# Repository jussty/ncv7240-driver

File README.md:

# NCV7240 x4 — ESP32 + USB-C PD EPR (24 V) Driver Board

A KiCad 8 project for a compact controller board that:

- Negotiates **24 V** from a USB-C **PD 3.1 EPR** source via the **AP33772S** sink controller.
- Hosts an **ESP32-S3** MCU for Wi-Fi/BT control, configuration and host comms.
- Drives **32 low-side switched outputs** at 24 V using **4 × NCV7240** octal low-side drivers (SPI-controlled).

> Status: skeleton — project files, design rules, net classes and BOM are in place. The schematic (`ncv7240-driver.kicad_sch`) and PCB (`ncv7240-driver.kicad_pcb`) are intentionally empty placeholders ready to be populated in KiCad 8.

---

## 1. System architecture

```
       USB-C (PD 3.1 EPR, up to 28 V / 5 A)
           │
           ▼
   ┌────────────────┐   I²C   ┌──────────────────────┐
   │   AP33772S     │◀───────▶│   ESP32-S3-WROOM-1   │
   │  PD EPR sink   │  (CFG)  │  (Wi-Fi / BT / USB)  │
   └──────┬─────────┘         └───────┬──────────────┘
          │ VBUS_OUT = 24 V           │ SPI (CS x4, SCK, MOSI, MISO)
          │                           │ + RSTB, /FSO IRQ
          ▼                           ▼
   ┌──────────────┐   ┌──────────────┐   ┌──────────────┐   ┌──────────────┐
   │  NCV7240 #1  │   │  NCV7240 #2  │   │  NCV7240 #3  │   │  NCV7240 #4  │
   │ 8 ch low-side│   │ 8 ch low-side│   │ 8 ch low-side│   │ 8 ch low-side│
   └──────┬───────┘   └──────┬───────┘   └──────┬───────┘   └──────┬───────┘
          ▼                  ▼                  ▼                  ▼
       OUT1..8            OUT9..16          OUT17..24          OUT25..32
       (loads sink to GND; common rail = 24 V)
```

- The AP33772S handles all CC negotiation/PPS/EPR; the ESP32 just configures the
  request profile over I²C and reads VBUS / status telemetry.
- The 4 NCV7240s share SCK/MOSI/MISO/RSTB/SI on a single SPI bus; each has its
  own **/CSB** from the ESP32. Output enable is per-channel via SPI control word.

## 2. Bill of materials (core)

| Ref       | Part                          | Pkg          | Notes                                    |
|-----------|-------------------------------|--------------|------------------------------------------|
| U1        | AP33772S                      | QFN-24       | USB-C PD 3.1 EPR sink controller         |
| U2        | ESP32-S3-WROOM-1-N8R8         | SMD module   | 8 MB flash, 8 MB PSRAM                   |
| U3..U6    | NCV7240ADQR2G                 | SSOP-24      | Octal low-side driver, SPI               |
| J1        | USB-C receptacle (EPR rated)  | TID/16-pin   | 5 A continuous, EPR cable required >3 A  |
| D1        | TVS for VBUS (e.g. SMBJ33A)   | SMB          | 33 V standoff                            |
| L1        | 10 µH @ 3 A ferrite/inductor  | 1210         | VBUS LC filter (optional)                |
| C_BULK    | 100 µF / 50 V × 2             | electrolytic | VBUS bulk on 24 V rail                   |
| FB1..FB4  | Ferrite bead, 600 Ω @ 100 MHz | 0603         | Per-NCV7240 V_PWR decoupling             |
| U7        | LDO/buck 24 V → 3.3 V (e.g. MP2451 or TPS62932) | SOT-23-6 | ≥500 mA for ESP32 peaks    |
| U8        | (optional) 3.3 V LDO          | SOT-23-5     | Clean rail for analog if needed          |
| Q_GATE    | P-MOSFET (e.g. DMP3098L)      | SOT-23       | Reverse-polarity / VBUS gate (optional)  |
| R_CS      | 1 % shunts                    | 0805         | If per-bank current sensing is desired   |

Plus per-channel flyback diodes/TVS if driving inductive loads (the NCV7240
has internal active clamp, but external TVS to 24 V rail is recommended for
solenoids/relays).

## 3. Net classes / design rules

Defined in `ncv7240-driver.kicad_pro`:

| Net class    | Track | Clearance | Vias        | Used for                              |
|--------------|-------|-----------|-------------|---------------------------------------|
| Default      | 0.25  | 0.20      | 0.6 / 0.3   | logic, SPI, I²C                       |
| Power_24V    | 0.80  | 0.40      | 0.9 / 0.4   | VBUS, 24 V plane feeds, OUTx pours    |
| USB_PD       | 0.40  | 0.25      | 0.7 / 0.3   | CC1/CC2, VBUS sense, D+/D- (90 Ω diff)|

## 4. Pin assignment (ESP32-S3 → NCVs / AP33772S)

| ESP32 pin | Net           | Goes to                                  |
|-----------|---------------|------------------------------------------|
| GPIO10    | SPI_CS1       | NCV7240 #1 /CSB                          |
| GPIO11    | SPI_CS2       | NCV7240 #2 /CSB                          |
| GPIO12    | SPI_CS3       | NCV7240 #3 /CSB                          |
| GPIO13    | SPI_CS4       | NCV7240 #4 /CSB                          |
| GPIO14    | SPI_SCK       | all NCV7240 SCLK                         |
| GPIO15    | SPI_MOSI      | all NCV7240 SI                           |
| GPIO16    | SPI_MISO      | all NCV7240 SO (open-drain, ext. pull-up)|
| GPIO17    | NCV_RSTB      | all NCV7240 /RSTB (active low, pull-up)  |
| GPIO18    | NCV_FSO       | all NCV7240 /FSO fault flag (IRQ)        |
| GPIO8     | I2C_SDA       | AP33772S SDA (+ 4.7 kΩ pull-up to 3V3)   |
| GPIO9     | I2C_SCL       | AP33772S SCL (+ 4.7 kΩ pull-up to 3V3)   |
| GPIO4     | PD_INT        | AP33772S /INT                            |
| EN        | reset btn     | per ESP32 standard wiring                |
| GPIO0     | boot btn      | per ESP32 standard wiring                |

> Avoid the strapping pins (GPIO0/3/45/46) and USB pins (19/20) for the
> dedicated nets above — already accounted for.

## 5. NCV7240 wiring notes

- Tie all `V_PWR` pins to the 24 V rail through individual ferrite beads
  + 100 nF + 10 µF local decoupling per IC.
- All `GND` pins tied to the solid 24 V-return ground pour.
- `SO` is open-drain; place one 10 kΩ pull-up to 3V3 on the shared MISO net.
- `/RSTB` shared and pulled up to 3V3 (10 kΩ); ESP32 drives low to reset all.
- `/FSO` shared open-drain fault flag → ESP32 IRQ, pulled up to 3V3.
- Daisy-chained SPI is **not** used here (independent /CSB per device is
  simpler and lets the ESP32 talk to any device individually at full clock).
- Each OUTx pad gets a generous copper pour and a screw terminal or 2.54 mm
  header per channel. For inductive loads, place a TVS/clamp diode from OUTx
  to the 24 V rail close to the load connector.

## 6. AP33772S notes

- Connect CC1/CC2 directly to the USB-C receptacle CC pins (no Rd needed —
  the AP33772S provides the sink termination).
- VBUS sense via internal divider; place 100 µF + 10 µF + 100 nF bulk on
  VBUS_OUT after the controller's NMOS pass switch.
- Pull `VPP` / `VDD` decoupling per datasheet (1 µF on VDD, 100 nF on VPP).
- The MCU configures the requested PDO (request 24 V/3 A EPR profile) via I²C
  at boot. Until configured the AP33772S falls back to its NVM defaults — flash
  the NVM with the desired default PDO request before deployment if you want
  the rail to come up without the ESP32.
- Add a SMBJ33A TVS across VBUS_OUT to GND.

## 7. Layout guidance

- 4-layer stack recommended: **Signal / GND / 24 V / Signal**.
- Keep the 24 V rail as a continuous pour on an inner layer; stitch with vias
  near each NCV7240 V_PWR pin.
- USB-C D+/D- routed as a 90 Ω differential pair, length-matched, away from
  the switching loads. (For PD-only operation D± are unused but route them
  anyway so the port can carry USB 2.0 data if desired.)
- Place the AP33772S close to the USB-C connector; keep the VBUS path short
  and wide (≥ 60 mil for 5 A).
- ESP32 antenna keep-out: leave ≥ 15 mm clearance and no copper under the
  antenna section of the module.
- Per-channel output traces: 0.8 mm minimum for 0.5 A loads, scale up for
  more. Add 2× thermal-relief pads at each NCV7240 exposed pad.

## 8. Loads — Bürkert Type 0127 valves (inductive)

Outputs drive **Bürkert Type 0127 rocker solenoid valves** (24 V DC,
**3 W ⇒ ≈125 mA per coil**). 32 channels × 125 mA = **4 A peak** on the
24 V rail — that's why we request a 24 V / 3-5 A EPR profile from the source.

Because the loads are inductive, every output has a **B260A-13-F** Schottky
(60 V / 2 A, SMA) freewheel diode:

  **Anode → OUTx, Cathode → +24V rail.**

When the NCV7240's low-side switch opens, the coil's collapsing field
drives OUTx above +24 V; the diode forward-biases at ≈0.7 V and recirculates
the coil current back into the rail, clamping OUTx to roughly `+24V + Vf`.
This is faster and dissipates less per-event than relying on the NCV7240's
internal active clamp (≈45 V).

> Place the freewheel diodes physically close to the screw terminal pads so
> the loop area between coil, diode and ground is minimised — important for
> EMI on a board switching 32 inductive loads.

## 9. Files

```
ncv7240-driver/
├── .gitignore
├── README.md
├── fp-lib-table  /  sym-lib-table
├── ncv7240-driver.kicad_pro   # KiCad 8 project, design rules + net classes
├── ncv7240-driver.kicad_sch   # generated by tools/gen_sch.py
├── ncv7240-driver.kicad_pcb   # generated by tools/gen_pcb.py
├── datasheets/                # versioned vendor PDFs
│   ├── ncv7240.pdf            (onsemi)
│   ├── ap33772s.pdf           (Diodes Inc)
│   ├── esp32-s3-wroom-1.pdf   (Espressif)
│   ├── b260a.pdf              (Diodes Inc — flyback Schottky)
│   └── burkert-0127.pdf       (Bürkert — load)
└── tools/
    ├── gen_sch.py             # deterministic schematic generator
    └── gen_pcb.py             # deterministic PCB skeleton generator
```

Regenerate after editing the generators:

```sh
python3 tools/gen_sch.py > ncv7240-driver.kicad_sch
python3 tools/gen_pcb.py > ncv7240-driver.kicad_pcb
```

Open `ncv7240-driver.kicad_pro` in **KiCad 8.0 or newer**. In Pcbnew:

1. **Tools → Update PCB from Schematic** to import all 30+ footprints
   from the standard KiCad libraries (you'll need them installed locally —
   they ship with KiCad).
2. Components arrive at the origin; drag them into the marked floorplan
   zones (visible on `User.Comments`).
3. Route, fill the GND and +24V zones, run DRC, export Gerbers to `gerbers/`.

## 10. Board floorplan (160 × 100 mm, 4-layer)

```
+----------------------------------------------------------------------+
|              NCV7240 x4 Driver — 24V PD EPR    (silkscreen header)   |
|                                                                      |
|  +--------+ +-------------+ +-------------+ +--------+ +----------+  |
|  |USB-C PD| | Buck 24V→3V3| |             | |  4×    | |  Screw   |  |
|  |  J1 U1 | |  U7 L1 C3   | |  ESP32-S3   | | NCV    | |  termi-  |  |
|  | C1/C2  | +-------------+ |   U2        | | 7240   | |  nals    |  |
|  |  D1    |                 | C4 C5       | | U3-U6  | | J2..J5   |  |
|  |        | (44-90, 6-36)   | R1..R5      | |        | |          |  |
|  |        |                 |             | |        | |          |  |
|  |        | +-------------+ |             | +--------+ +----------+  |
|  |        | |             | |             | | Flyback diode field   |  |
|  |        | |    ESP32    | |             | | D2..D33  B260A-SMA    |  |
|  | (4-44, | |  (44-90,    | | (44-90,     | | (90-156,              |  |
|  |  6-60) | |   36-96)    | |  36-96)     | |  60-96)               |  |
|  +--------+ +-------------+ +-------------+ +--------+ +----------+  |
|                                                                      |
+----------------------------------------------------------------------+
```

4-layer stackup: **F.Cu / GND / +24V / B.Cu** (1.6 mm FR4, ENIG finish).

## 9. License

Hardware: CERN-OHL-S v2 (recommended) — adjust to your needs.

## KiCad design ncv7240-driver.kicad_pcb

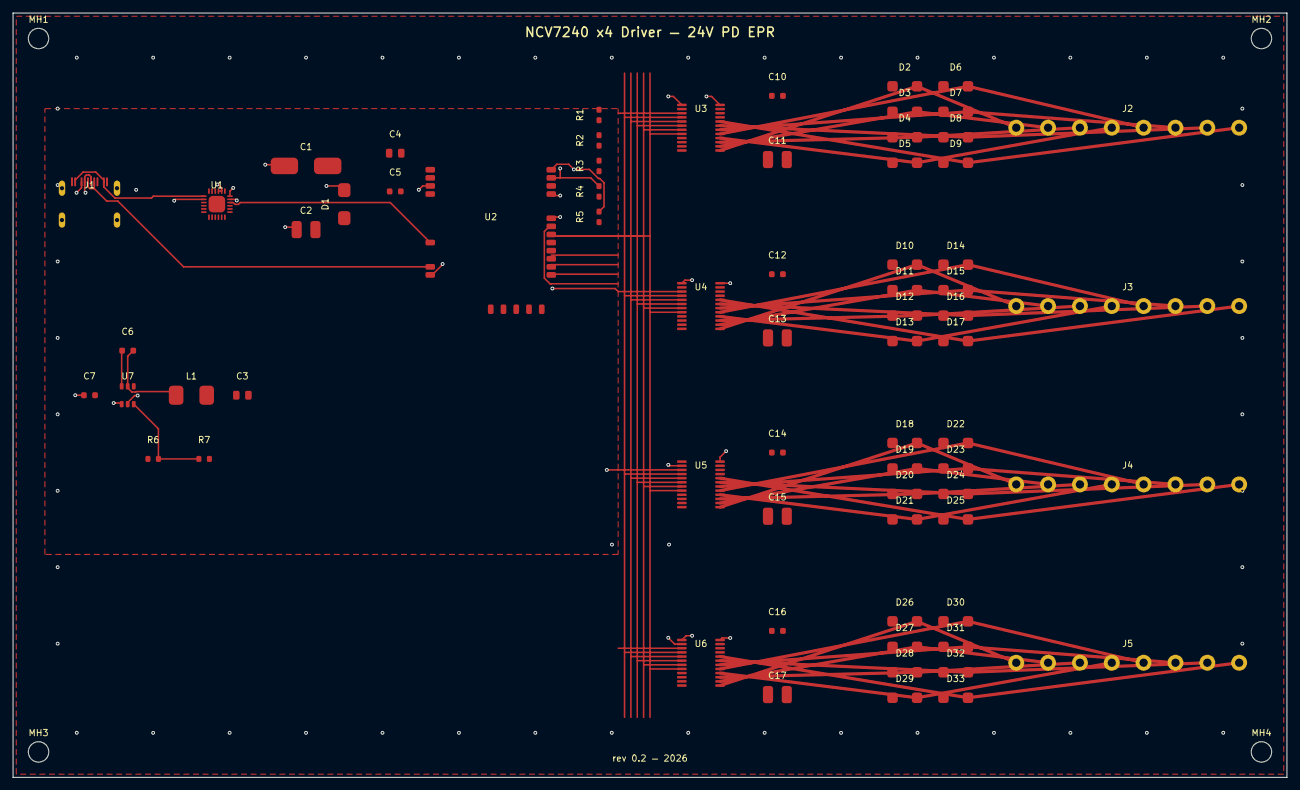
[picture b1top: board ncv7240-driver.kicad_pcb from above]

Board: 4 copper layers, 200.0 x 120.0 mm, 72 parts (0 on the bottom side), 56 nets.

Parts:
C1: 100uF/50V; CP_Elec_10x10.5
C2, C11, C13, C15, C17: 10uF/50V; C_1210_3225Metric
C3: 22uF; C_0805_2012Metric
C4: 10uF; C_0805_2012Metric
C5, C6, C7, C10, C12, C14, C16: 100nF; C_0603_1608Metric
D1: SMBJ33A; D_SMB
D2, D3, D4, D5, D6, D7, D8, D9, D10, D11, D12, D13, D14, D15, D16, D17, D18, D19, D20, D21, D22, D23, D24, D25, D26, D27, D28, D29, D30, D31, D32, D33: B260A; D_SMA
J1: USB-C; USB_C_Receptacle_HRO_TYPE-C-31-M-12
J2: OUT1-8; TerminalBlock_Phoenix_MKDS-1,5-8_1x08_P5.00mm_Horizontal
J3: OUT9-16; TerminalBlock_Phoenix_MKDS-1,5-8_1x08_P5.00mm_Horizontal
J4: OUT17-24; TerminalBlock_Phoenix_MKDS-1,5-8_1x08_P5.00mm_Horizontal
J5: OUT25-32; TerminalBlock_Phoenix_MKDS-1,5-8_1x08_P5.00mm_Horizontal
L1: 4.7uH/2A; L_Bourns-SRN6045TA
MH1, MH2, MH3, MH4: M3; MountingHole_3.2mm_M3
R1, R2, R3: 10k; R_0603_1608Metric
R4, R5: 4.7k; R_0603_1608Metric
R6: 100k; R_0603_1608Metric
R7: 20k; R_0603_1608Metric
U1: AP33772S; QFN-24-1EP_4x4mm_P0.5mm_EP2.6x2.6mm
U2: ESP32-S3-WROOM-1
U3, U4, U5, U6: NCV7240; SSOP-24_5.3x8.2mm_P0.65mm
U7: TPS62932; SOT-23-6

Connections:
+3V3: C3.1, C4.1, C5.1, L1.2, R1.1, R2.1, R3.1, R4.1, R5.1, R6.1, U1.4, U2.2, U3.2, U4.2, U5.2, U6.2
+24V: C1.1, C2.1, C7.1, C10.1, C11.1, C12.1, C13.1, C14.1, C15.1, C16.1, C17.1, D1.2, D2.1, D3.1, D4.1, D5.1, D6.1, D7.1, D8.1, D9.1, D10.1, D11.1, D12.1, D13.1, D14.1, D15.1, D16.1, D17.1, D18.1, D19.1, D20.1, D21.1, D22.1, D23.1, D24.1, D25.1, D26.1, D27.1, D28.1, D29.1, D30.1, D31.1, D32.1, D33.1, U1.20, U1.21, U3.1, U3.24, U4.1, U4.24, U5.1, U5.24, U6.1, U6.24, U7.6
BST: C6.1, U7.1
CC1: J1.4, U1.2
CC2: J1.9, U1.3
EN_3V3: U2.3, U7.5
FB: R6.2, R7.1, U7.4
GND: C1.2, C2.2, C3.2, C4.2, C5.2, C7.2, C10.2, C11.2, C12.2, C13.2, C14.2, C15.2, C16.2, C17.2, D1.1, J1.1, J1.12, J1.SH, R7.2, U1.5, U1.6, U1.7, U1.8, U1.9, U1.10, U1.11, U1.12, U1.13, U1.14, U1.15, U1.22, U1.23, U1.24, U1.25, U2.1, U2.27, U2.37, U2.38, U2.39, U2.40, U2.41, U3.9, U3.10, U3.11, U3.12, U3.21, U3.22, U3.23, U4.9, U4.10, U4.11, U4.12, U4.21, U4.22, U4.23, U5.9, U5.10, U5.11, U5.12, U5.21, U5.22, U5.23, U6.9, U6.10, U6.11, U6.12, U6.21, U6.22, U6.23, U7.3
I2C_SCL: R5.2, U1.17, U2.17
I2C_SDA: R4.2, U1.18, U2.18
NCV_FSOB: R3.2, U2.30, U3.8, U4.8, U5.8, U6.8
NCV_RSTB: R2.2, U2.29, U3.7, U4.7, U5.7, U6.7
OUT1: D2.2, J2.1, U3.13
OUT2: D3.2, J2.2, U3.14
OUT3: D4.2, J2.3, U3.15
OUT4: D5.2, J2.4, U3.16
OUT5: D6.2, J2.5, U3.17
OUT6: D7.2, J2.6, U3.18
OUT7: D8.2, J2.7, U3.19
OUT8: D9.2, J2.8, U3.20
OUT9: D10.2, J3.1, U4.13
OUT10: D11.2, J3.2, U4.14
OUT11: D12.2, J3.3, U4.15
OUT12: D13.2, J3.4, U4.16
OUT13: D14.2, J3.5, U4.17
OUT14: D15.2, J3.6, U4.18
OUT15: D16.2, J3.7, U4.19
OUT16: D17.2, J3.8, U4.20
OUT17: D18.2, J4.1, U5.13
OUT18: D19.2, J4.2, U5.14
OUT19: D20.2, J4.3, U5.15
OUT20: D21.2, J4.4, U5.16
OUT21: D22.2, J4.5, U5.17
OUT22: D23.2, J4.6, U5.18
OUT23: D24.2, J4.7, U5.19
OUT24: D25.2, J4.8, U5.20
OUT25: D26.2, J5.1, U6.13
OUT26: D27.2, J5.2, U6.14
OUT27: D28.2, J5.3, U6.15
OUT28: D29.2, J5.4, U6.16
OUT29: D30.2, J5.5, U6.17
OUT30: D31.2, J5.6, U6.18
OUT31: D32.2, J5.7, U6.19
OUT32: D33.2, J5.8, U6.20
PD_INT: U1.16, U2.10
SPI_CS1: U2.19, U3.3
SPI_CS2: U2.20, U4.3
SPI_CS3: U2.23, U5.3
SPI_CS4: U2.24, U6.3
SPI_MISO: R1.2, U2.28, U3.6, U4.6, U5.6, U6.6
SPI_MOSI: U2.26, U3.5, U4.5, U5.5, U6.5
SPI_SCK: U2.25, U3.4, U4.4, U5.4, U6.4
SW: C6.2, L1.1, U7.2
USB_D+: J1.5, J1.7, U2.14
USB_D-: J1.6, J1.8, U2.13
VBUS: J1.2, J1.11, U1.1

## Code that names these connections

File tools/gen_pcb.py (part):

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
# ---- Buck 24V → 3.3V (x=10..50, y=55..80) ----
place_sot23_6("U7", "TPS62932", 18, 60, 0, pin_nets=[
    # SOT-23-6: pin1=BST,2=SW,3=GND,4=FB,5=EN,6=VIN  (TPS62932)
    "BST","SW","GND","FB","EN_3V3","+24V"
])
place_inductor("L1", "4.7uH/2A", 28, 60, 0, "SW", "+3V3")
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    "NCV_FSOB": 100.0,
}
BUS_PIN_K = {  # pin number on NCV → k offset from top of left column
    "SPI_SCK":  3,   # pin 4
    "SPI_MOSI": 4,   # pin 5
    "SPI_MISO": 5,   # pin 6
    "NCV_RSTB": 6,   # pin 7
    "NCV_FSOB": 7,   # pin 8
}
y_top = ncv_y_centres[0] - 0.65*5.5
y_bot = ncv_y_centres[-1] + 0.65*5.5
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
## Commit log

2026-05-11 Initial KiCad project: 4x NCV7240 + ESP32-S3 + AP33772S PD EPR 24V
2026-05-11 Draw block-diagram schematic with all symbols embedded for kicanvas
    - Python generator at tools/gen_sch.py produces ncv7240-driver.kicad_sch
    - All symbol definitions embedded inline (kicanvas has no external libs)
    - Components: USB-C, AP33772S, ESP32-S3-WROOM-1, 4x NCV7240, buck reg,
    bulk/decoupling caps, TVS, pull-ups, 8-pin output screw terminals
    - Connectivity via KiCad global labels (SPI bus, I2C, power rails, OUT1..32)
    - A2 sheet, deterministic UUIDs for clean diffs
2026-05-12 Add 32 flyback diodes, real footprints, and parts datasheets
    - 32× B260A-13-F Schottky (60V / 2A SMA) freewheel diodes — one per
    output, anode→OUTx, cathode→+24V, for Bürkert Type 0127 valve coils
    (3 W @ 24 V ≈ 125 mA, inductive)
    - Footprints assigned for all parts:
    - NCV7240 SSOP-24 P0.65
    - AP33772S QFN-24 4x4 EP2.6
2026-05-12 Start PCB layout: 4-layer 160x100mm with floorplan and pours
    - tools/gen_pcb.py — deterministic PCB skeleton generator
    - 160 × 100 mm rectangular board outline on Edge.Cuts
    - 4-layer stackup: F.Cu / GND (In1) / +24V (In2) / B.Cu, 1.6 mm FR4 ENIG
    - 4× M3 mounting holes inset 4 mm from corners
    - 57 nets pre-declared (matches schematic: GND/+24V/+3V3/VBUS/CC/I2C/
    SPI/PD/USB/RST_BTN/BOOT_BTN + OUT1..OUT32)
2026-05-12 Pre-place all 72 footprints into floorplan with net assignments
    200×120 mm 4-layer board, all components placed with embedded pad
    geometry so kicanvas can render the board directly. After opening in
    KiCad, 'Tools → Update PCB from Schematic' will refresh footprints
    to the full library geometry while preserving placement and nets.
    Placement (left → right):
    - USB-C J1 + AP33772S U1 + bulk caps C1/C2 + TVS D1
2026-05-12 Route OUTx output paths and SPI/control bus
    - 32× output traces routed on F.Cu (0.5 mm width):
    NCV pin → flyback diode anode → screw terminal pin
    - Shared SPI/control bus on F.Cu (0.25 mm) in the gap between
    ESP32 and the NCV stack:
    SPI_SCK x=96
    SPI_MOSI x=97
2026-05-12 pcb: add F.Cu GND zone, populate fp-lib-table, render board
    - Add low-priority F.Cu GND copper pour so perimeter stitching vias
    have something to anchor to on the top side.
    - Populate fp-lib-table with standard KiCad footprint libraries
    (Resistor_SMD, Capacitor_SMD, Diode_SMD, Package_SO, Package_DFN_QFN,
    RF_Module, Connector_USB, TerminalBlock_Phoenix, MountingHole, etc.)
    so KiCad GUI can resolve real library footprints when the user runs
2026-05-12 pcb: freerouting headless round-trip (partial)
    Set up a headless DSN→freerouting→SES round-trip:
    - DSN export via pcbnew Python bindings (ExportSpecctraDSN)
    - freerouting v2.2.3 run with --gui-disabled, 30 router passes,
    5 optimizer passes, 10-minute job timeout
    - SES import via pcbnew.ImportSpecctraSES
    Result: partial autoroute. 137 net segments at start, 98 still
2026-05-12 sch: strip library prefix from child unit symbol names
    KiCad 10's parser rejects names like "power:+24V_0_1" with
    "Invalid symbol unit name prefix power:+24V_0_1". Inside a
    lib_symbols entry, the parent symbol carries the library prefix
    ("power:+24V") but the child unit symbols must use only the
    short form ("+24V_0_1", "+24V_1_1").
    Fixes the make_sym() and pwr_sym() helpers in gen_sch.py to
